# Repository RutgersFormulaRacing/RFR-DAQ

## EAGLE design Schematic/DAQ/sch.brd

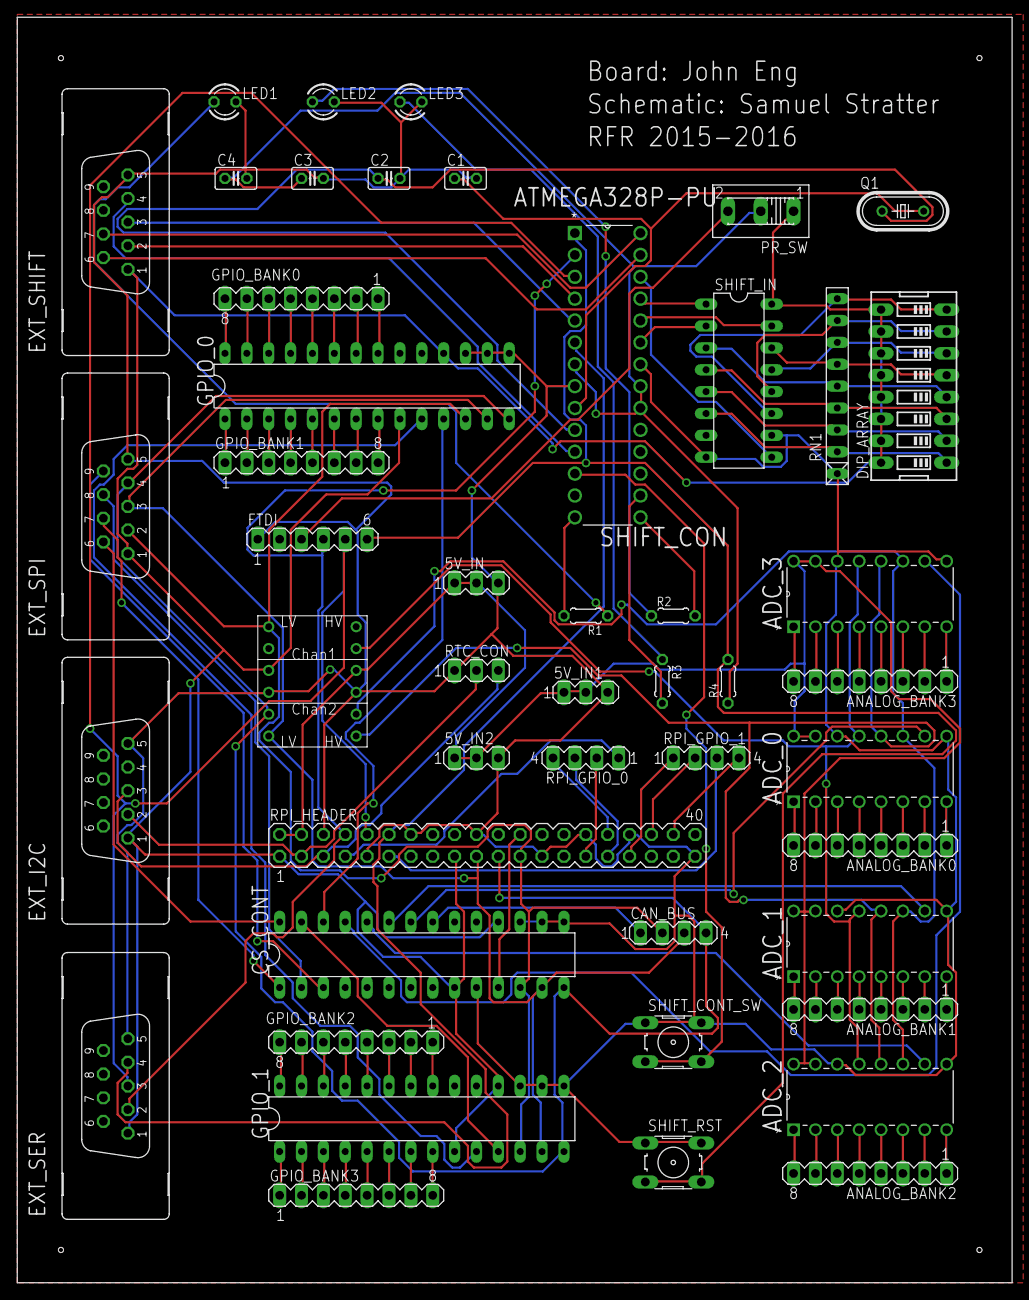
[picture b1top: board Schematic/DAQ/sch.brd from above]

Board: 2 copper layers, 115.5 x 147.0 mm, 48 parts (0 on the bottom side), 128 nets.

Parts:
5V_IN, 5V_IN1, 5V_IN2: MA03-1
ADC_0, ADC_1, ADC_2, ADC_3: MCP3208-CI/P; DIP254P762X432-16
ANALOG_BANK0, ANALOG_BANK1, ANALOG_BANK2, ANALOG_BANK3: MA08-1
C1, C2, C3, C4: C025-025X050
CAN_BUS: MA04-1
CS_CONT: MCP23S17SP; DIL28-3
DIP_ARRAY: DIPSWITCH-08
EXT_I2C: F09VB
EXT_SER: F09VB
EXT_SHIFT: F09VB
EXT_SPI: F09VB
FTDI: MA06-1
GPIO_0, GPIO_1: MCP23S17SP; DIL28-3
GPIO_BANK0, GPIO_BANK1, GPIO_BANK2, GPIO_BANK3: MA08-1
LED1, LED2, LED3: LED3MM
LOGIC_SHIFT: LOGIC_LEVEL_CONVERTER
PR_SW: 255SB
Q1: HC49/S
R1, R2, R3, R4: 0204/5
RN1: RN-9
RPI_GPIO_0, RPI_GPIO_1: MA04-1
RPI_HEADER: MA20-2
RTC_CON: MA03-1
SHIFT_CON: ATMEGA328P-PU; DIP254P762X457-28
SHIFT_CONT_SW: B3F-10XX
SHIFT_IN: 74LS165N; DIL16
SHIFT_RST: B3F-10XX

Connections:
3V3: CS_CONT.9, CS_CONT.18, DIP_ARRAY.9, DIP_ARRAY.10, DIP_ARRAY.11, DIP_ARRAY.12, DIP_ARRAY.13, DIP_ARRAY.14, DIP_ARRAY.15, DIP_ARRAY.16, EXT_I2C.1, EXT_SER.1, EXT_SHIFT.1, EXT_SPI.1, GPIO_0.9, GPIO_0.18, GPIO_1.9, GPIO_1.18, LOGIC_SHIFT.P$3, PR_SW.1, RPI_HEADER.1, RPI_HEADER.17, SHIFT_IN.16
5V: 5V_IN.1, 5V_IN.2, 5V_IN1.1, 5V_IN1.2, 5V_IN2.1, 5V_IN2.2, ADC_0.15, ADC_0.16, ADC_1.15, ADC_1.16, ADC_2.15, ADC_2.16, ADC_3.15, ADC_3.16, LOGIC_SHIFT.P$10, RPI_HEADER.2, RPI_HEADER.4
CAN_CS: CAN_BUS.1, CS_CONT.21
DAQ_CS0: CS_CONT.11, RPI_HEADER.24
DAQ_MISO: CAN_BUS.4, CS_CONT.14, EXT_SPI.4, GPIO_0.14, GPIO_1.14, LOGIC_SHIFT.P$5, RPI_HEADER.21
DAQ_MOSI: CAN_BUS.3, CS_CONT.13, EXT_SPI.3, GPIO_0.13, GPIO_1.13, LOGIC_SHIFT.P$6, RPI_HEADER.19
DAQ_RX: EXT_SER.3, FTDI.5, RPI_HEADER.10, SHIFT_CON.3
DAQ_SCK: CAN_BUS.2, CS_CONT.12, EXT_SPI.2, GPIO_0.12, GPIO_1.12, LOGIC_SHIFT.P$1, RPI_HEADER.23
DAQ_SCL: EXT_I2C.3, RPI_HEADER.5, RTC_CON.3
DAQ_SDA: EXT_I2C.2, RPI_HEADER.3, RTC_CON.2
DAQ_SYNC: EXT_SER.4, RPI_HEADER.12, SHIFT_CON.6
DAQ_TX: EXT_SER.2, FTDI.4, RPI_HEADER.8, SHIFT_CON.2
EXT_CS0: CS_CONT.28, EXT_SPI.6
EXT_CS1: CS_CONT.1, EXT_SPI.7
EXT_CS2: CS_CONT.2, EXT_SPI.8
EXT_CS3: CS_CONT.3, EXT_SPI.9
GND: 5V_IN.3, 5V_IN1.3, 5V_IN2.3, ADC_0.9, ADC_0.14, ADC_1.9, ADC_1.14, ADC_2.9, ADC_2.14, ADC_3.9, ADC_3.14, C1.2, C2.2, C3.2, C4.2, CS_CONT.10, CS_CONT.15, CS_CONT.16, CS_CONT.17, EXT_I2C.5, EXT_SER.5, EXT_SHIFT.5, EXT_SPI.5, FTDI.1, GPIO_0.15, GPIO_0.16, GPIO_0.17, GPIO_1.15, GPIO_1.16, GPIO_1.17, LED1.K, LED2.K, LED3.K, LOGIC_SHIFT.P$4, LOGIC_SHIFT.P$9, RN1.1, RPI_HEADER.6, RPI_HEADER.9, RPI_HEADER.14, RPI_HEADER.20, RPI_HEADER.25, RPI_HEADER.30, RPI_HEADER.34, RPI_HEADER.39, RTC_CON.1, SHIFT_CON.8, SHIFT_CON.22, SHIFT_CONT_SW.1, SHIFT_CONT_SW.2, SHIFT_IN.8, SHIFT_IN.10, SHIFT_RST.1, SHIFT_RST.2
GPIO_4: RPI_GPIO_0.1, RPI_HEADER.7
GPIO_5: RPI_GPIO_0.2, RPI_HEADER.29
GPIO_6: RPI_GPIO_0.3, RPI_HEADER.31
GPIO_12: RPI_GPIO_0.4, RPI_HEADER.32
GPIO_13: RPI_GPIO_1.1, RPI_HEADER.33
GPIO_16: RPI_GPIO_1.2, RPI_HEADER.36
GPIO_17: RPI_GPIO_1.3, RPI_HEADER.11
GPIO_20: RPI_GPIO_1.4, RPI_HEADER.38
GPIO_CS0: CS_CONT.26, GPIO_0.11
GPIO_CS1: CS_CONT.27, GPIO_1.11
unnamed: GPIO_1.21, GPIO_BANK2.1
unnamed: GPIO_1.22, GPIO_BANK2.2
unnamed: GPIO_1.23, GPIO_BANK2.3
unnamed: GPIO_0.10, GPIO_1.10
unnamed: ADC_3.1, ANALOG_BANK3.8
unnamed: ADC_3.2, ANALOG_BANK3.7
unnamed: ADC_0.10, CS_CONT.22
unnamed: ADC_1.10, CS_CONT.23
unnamed: ADC_2.10, CS_CONT.24
unnamed: DIP_ARRAY.8, RN1.9, SHIFT_IN.11
unnamed: DIP_ARRAY.7, RN1.8, SHIFT_IN.12
unnamed: DIP_ARRAY.6, RN1.7, SHIFT_IN.13
unnamed: DIP_ARRAY.5, RN1.6, SHIFT_IN.14
unnamed: DIP_ARRAY.4, RN1.5, SHIFT_IN.3
unnamed: DIP_ARRAY.3, RN1.4, SHIFT_IN.4
unnamed: DIP_ARRAY.2, RN1.3, SHIFT_IN.5
unnamed: DIP_ARRAY.1, RN1.2, SHIFT_IN.6
unnamed: GPIO_1.24, GPIO_BANK2.4
unnamed: GPIO_1.25, GPIO_BANK2.5
unnamed: GPIO_1.26, GPIO_BANK2.6
unnamed: LED3.A, R3.1
unnamed: LED2.A, R2.1
unnamed: LED1.A, R1.1
unnamed: R1.2, SHIFT_CON.14
unnamed: R2.2, SHIFT_CON.15
unnamed: R3.2, SHIFT_CON.16
unnamed: GPIO_1.27, GPIO_BANK2.7
unnamed: ADC_0.12, ADC_1.12, ADC_2.12, ADC_3.12, LOGIC_SHIFT.P$7
unnamed: ADC_0.11, ADC_1.11, ADC_2.11, ADC_3.11, LOGIC_SHIFT.P$8
unnamed: ADC_0.13, ADC_1.13, ADC_2.13, ADC_3.13, LOGIC_SHIFT.P$11
unnamed: GPIO_1.28, GPIO_BANK2.8
unnamed: GPIO_1.1, GPIO_BANK3.1
unnamed: GPIO_1.2, GPIO_BANK3.2
unnamed: ADC_3.10, CS_CONT.25
unnamed: GPIO_1.3, GPIO_BANK3.3
unnamed: GPIO_1.4, GPIO_BANK3.4
unnamed: GPIO_1.5, GPIO_BANK3.5
unnamed: GPIO_1.6, GPIO_BANK3.6
unnamed: GPIO_1.7, GPIO_BANK3.7
unnamed: GPIO_1.8, GPIO_BANK3.8
unnamed: GPIO_0.8, GPIO_BANK1.8
unnamed: GPIO_0.7, GPIO_BANK1.7
unnamed: GPIO_0.6, GPIO_BANK1.6
unnamed: GPIO_0.5, GPIO_BANK1.5
unnamed: GPIO_0.4, GPIO_BANK1.4
unnamed: GPIO_0.3, GPIO_BANK1.3
unnamed: GPIO_0.2, GPIO_BANK1.2
unnamed: GPIO_0.1, GPIO_BANK1.1
unnamed: GPIO_0.28, GPIO_BANK0.8
unnamed: GPIO_0.27, GPIO_BANK0.7
unnamed: GPIO_0.26, GPIO_BANK0.6
unnamed: GPIO_0.25, GPIO_BANK0.5
unnamed: GPIO_0.24, GPIO_BANK0.4
unnamed: GPIO_0.23, GPIO_BANK0.3
unnamed: GPIO_0.22, GPIO_BANK0.2
unnamed: GPIO_0.21, GPIO_BANK0.1
unnamed: ADC_3.3, ANALOG_BANK3.6
unnamed: ADC_3.4, ANALOG_BANK3.5
unnamed: ADC_3.5, ANALOG_BANK3.4
unnamed: ADC_3.6, ANALOG_BANK3.3
unnamed: ADC_3.7, ANALOG_BANK3.2
unnamed: ADC_3.8, ANALOG_BANK3.1
unnamed: ADC_2.8, ANALOG_BANK2.1
unnamed: ADC_2.7, ANALOG_BANK2.2
unnamed: ADC_2.6, ANALOG_BANK2.3
unnamed: ADC_2.5, ANALOG_BANK2.4
unnamed: ADC_2.4, ANALOG_BANK2.5
unnamed: ADC_2.3, ANALOG_BANK2.6
unnamed: ADC_2.2, ANALOG_BANK2.7
unnamed: ADC_2.1, ANALOG_BANK2.8
unnamed: ADC_1.8, ANALOG_BANK1.1
unnamed: ADC_1.7, ANALOG_BANK1.2
unnamed: ADC_1.6, ANALOG_BANK1.3
unnamed: ADC_1.5, ANALOG_BANK1.4
unnamed: ADC_1.4, ANALOG_BANK1.5
unnamed: ADC_1.3, ANALOG_BANK1.6
unnamed: ADC_1.2, ANALOG_BANK1.7
unnamed: ADC_1.1, ANALOG_BANK1.8
unnamed: ADC_0.8, ANALOG_BANK0.1
unnamed: ADC_0.7, ANALOG_BANK0.2
unnamed: ADC_0.6, ANALOG_BANK0.3
unnamed: ADC_0.5, ANALOG_BANK0.4
unnamed: ADC_0.4, ANALOG_BANK0.5
unnamed: ADC_0.3, ANALOG_BANK0.6
unnamed: ADC_0.2, ANALOG_BANK0.7
unnamed: ADC_0.1, ANALOG_BANK0.8
PR_RST: FTDI.6, R4.2, SHIFT_CON.1, SHIFT_RST.3, SHIFT_RST.4
PR_VCC: FTDI.3, PR_SW.3
SDN_OUT: EXT_SHIFT.7, SHIFT_CON.28
SH_EN: EXT_SHIFT.4, SHIFT_CON.11
SH_HLD: SHIFT_CON.25, SHIFT_IN.1
SH_INH: SHIFT_CON.24, SHIFT_IN.15
SH_OUT: SHIFT_CON.26, SHIFT_IN.9
SH_SER: SHIFT_CON.23, SHIFT_IN.2
SH_SHDN: EXT_SHIFT.3, SHIFT_CON.5
SH_SHUP: EXT_SHIFT.2, SHIFT_CON.4
SH_SW: SHIFT_CON.12, SHIFT_CONT_SW.3, SHIFT_CONT_SW.4
SH_VCC: C3.1, C4.1, PR_SW.2, R4.1, SHIFT_CON.7, SHIFT_CON.20, SHIFT_CON.21
SU_OUT: EXT_SHIFT.6, SHIFT_CON.27
XTAL1: C1.1, Q1.2, SHIFT_CON.9
XTAL2: C2.1, Q1.1, SHIFT_CON.10

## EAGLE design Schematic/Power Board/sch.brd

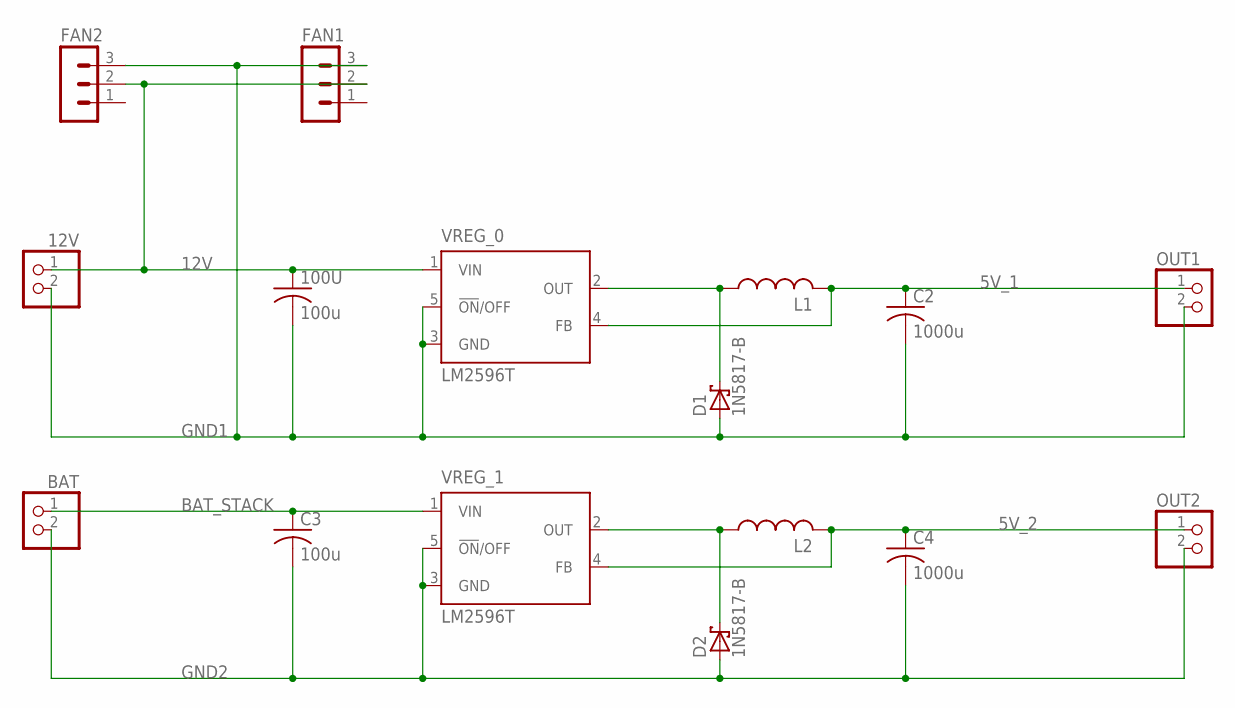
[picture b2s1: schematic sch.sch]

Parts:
12V: PINHD-1X2; 1X02
100U: 100u; C025-030X050
BAT: PINHD-1X2; 1X02
C2, C4: 1000u; C025-030X050
C3: 100u; C025-030X050
D1, D2: 1N5817-B; DO41-7.6
FAN1, FAN2: MA03-1
L1, L2: L-US6000-XXX-RC; 6000-XXXX-RC
OUT1, OUT2: PINHD-1X2; 1X02
VREG_0, VREG_1: LM2596T; T05D

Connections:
5V_1: C2.1, L1.2, OUT1.1, VREG_0.4 (FB)
5V_2: C4.1, L2.2, OUT2.1, VREG_1.4 (FB)
12V: 12V.1, 100U.1, FAN1.2, FAN2.2, VREG_0.1 (VIN)
BAT_STACK: BAT.1, C3.1, VREG_1.1 (VIN)
GND1: 12V.2, 100U.2, C2.2, D1.A, FAN1.3, FAN2.3, OUT1.2, VREG_0.3 (GND), VREG_0.5 (!ON!/OFF)
GND2: BAT.2, C3.2, C4.2, D2.A, OUT2.2, VREG_1.3 (GND), VREG_1.5 (!ON!/OFF)
unnamed: D1.C, L1.1, VREG_0.2 (OUT)
unnamed: D2.C, L2.1, VREG_1.2 (OUT)

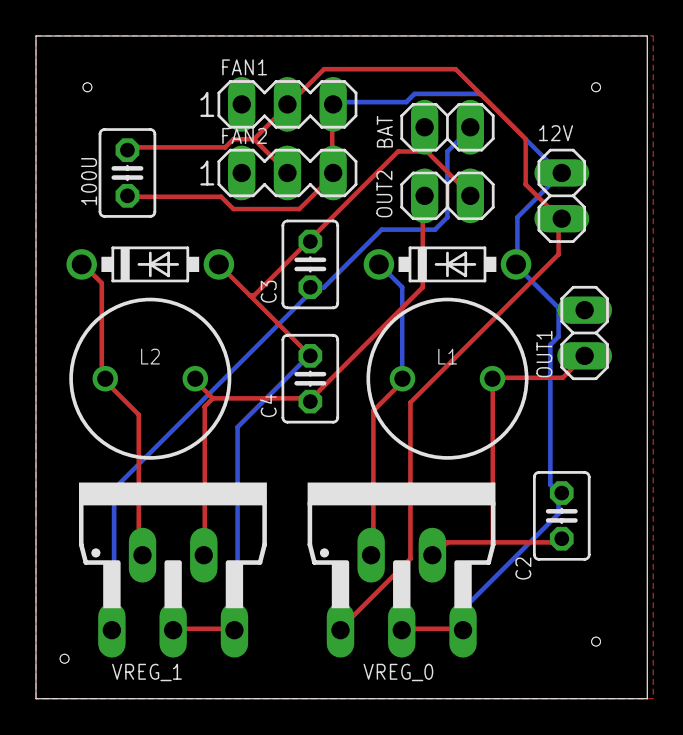
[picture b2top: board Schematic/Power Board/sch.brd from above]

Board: 2 copper layers, 34.0 x 36.8 mm, 16 parts (0 on the bottom side), 8 nets.

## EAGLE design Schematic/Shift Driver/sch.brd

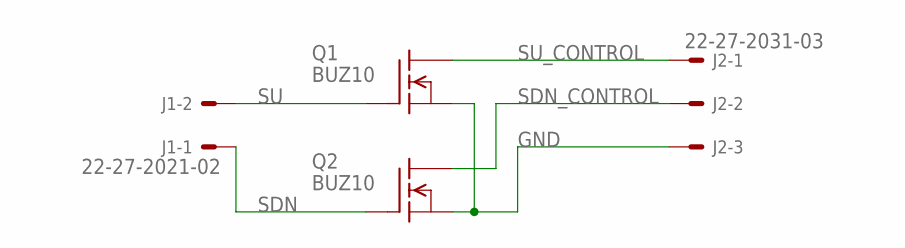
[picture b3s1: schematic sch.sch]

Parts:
J1: 22-27-2021-02; 6410-02
J2: 22-27-2031-03; 6410-03
Q1, Q2: BUZ10; TO220

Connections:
GND: J2.3, Q1.3 (S), Q2.3 (S)
SDN: J1.1, Q2.1 (G)
SDN_CONTROL: J2.2, Q2.2 (D)
SU: J1.2, Q1.1 (G)
SU_CONTROL: J2.1, Q1.2 (D)

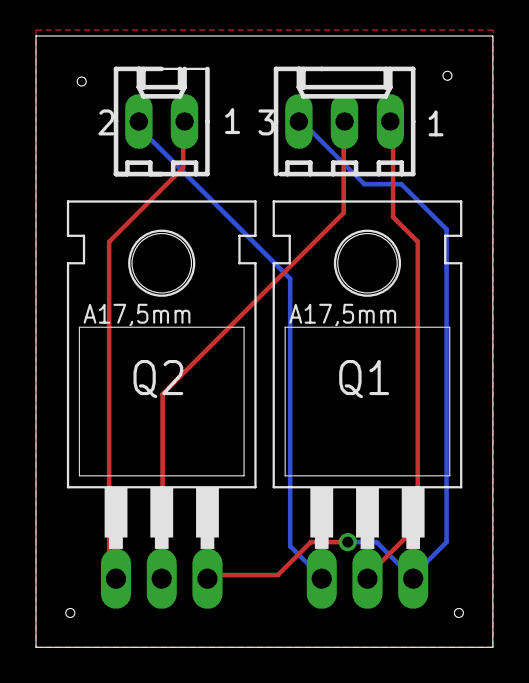
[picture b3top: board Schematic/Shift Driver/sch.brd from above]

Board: 2 copper layers, 25.4 x 34.0 mm, 4 parts (0 on the bottom side), 5 nets.

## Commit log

2015-08-10 Added functioning server
2015-08-10 Removed empty file
2015-08-11 Updated Config
2015-09-04 Changes!!
2015-10-23 Schematic
2015-10-24 Need paid version
2015-11-20 Errors to be fixed
2015-12-04 Schematic updates
2015-12-04 Folders
2015-12-11 ShiftDriver Board made
2015-12-11 basic board layout made
2015-12-11 Started board
2015-12-13 DAQ Board Done
2015-12-14 Fixes
2015-12-18 DAQ board made
2015-12-18 SPI Board done
2015-12-18 Shift Driver board done
2015-12-18 Power Board done
2015-12-29 Final Design Rev. 1
2016-01-08 Config modifications
2016-01-08 File Rename
2016-01-08 MLX90616 Support
2016-01-08 File Renaming
2016-01-09 Reorganizing
2016-03-06 Changesgit config --global user.name humanharddrive
2016-04-23 shift controller code started
2016-04-23 shift controller ISRs need filling
2016-04-26 shift controller is finished i think
2016-05-04 Added gear count

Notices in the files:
parts and their libraries:
SparkFun-Electromechanical: Licensing: Creative Commons ShareAlike 4.0 International - https://creativecommons.org/licenses/by-sa/4.0
